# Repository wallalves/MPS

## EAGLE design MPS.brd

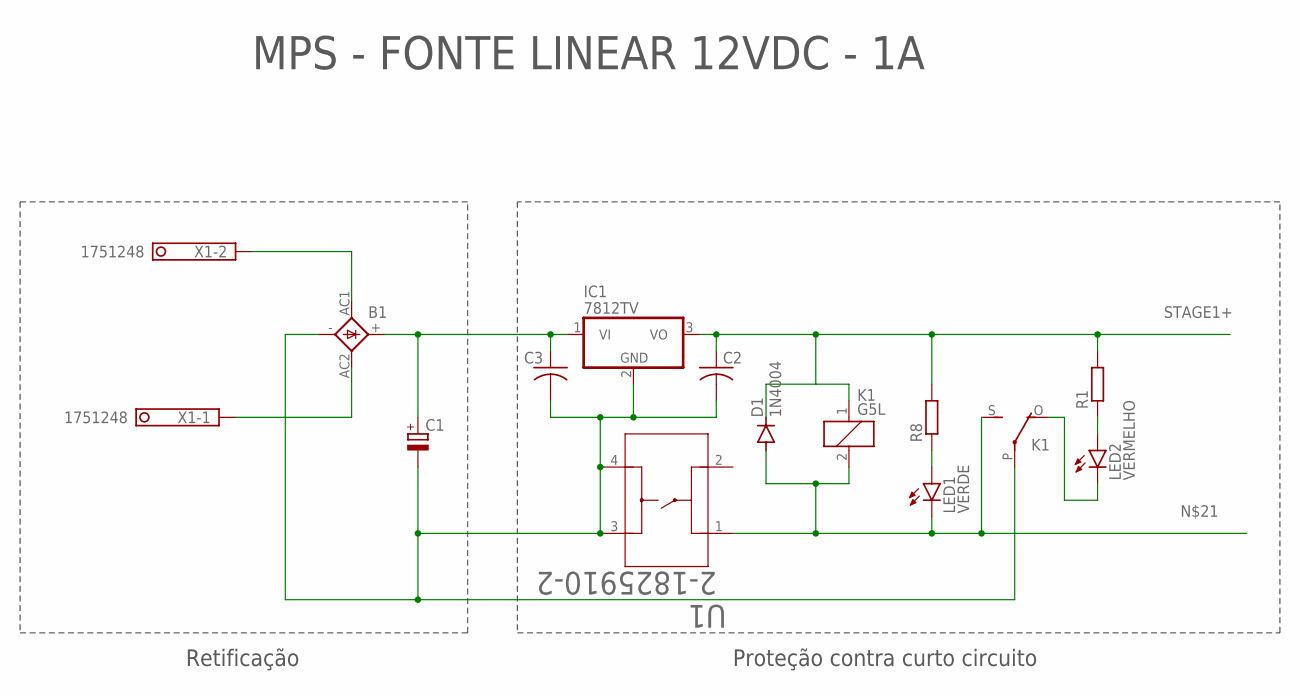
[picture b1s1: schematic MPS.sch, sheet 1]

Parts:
B1: 2KBB-R
C1: CPOL-EUE2.5-7; E2,5-7
C2, C3: C-US050-035X075; C050-035X075
D1: 1N4004; DO41-10
IC1: 7812TV; TO220V
K1: G5L; G5LE
LED1: VERDE; LED3MM
LED2: VERMELHO; LED3MM
R1, R8: R-EU_0207/7; 0207/7
U1: 2-1825910-2; SWITCH_2-1825910-2
X1: 1751248

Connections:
unnamed: B1.AC2, X1.1
unnamed: K1.O, LED2.K (C)
unnamed: LED1.A, R8.1
unnamed: B1.AC1, X1.2
unnamed: LED2.A, R1.1
unnamed: B1.+, C1.+, C3.1, IC1.1 (VI)
unnamed: D1.A, K1.2, K1.S, LED1.K (C), U1.1
STAGE1+: C2.1, D1.C, IC1.3 (VO), K1.1, R1.2, R8.2; also elsewhere on the board
STAGE1-: B1.-, C1.-, C2.2, C3.2, IC1.2 (GND), K1.P, U1.3, U1.4; also elsewhere on the board

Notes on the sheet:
MPS - FONTE LINEAR 12VDC - 1A
Retificação
Proteção contra curto circuito

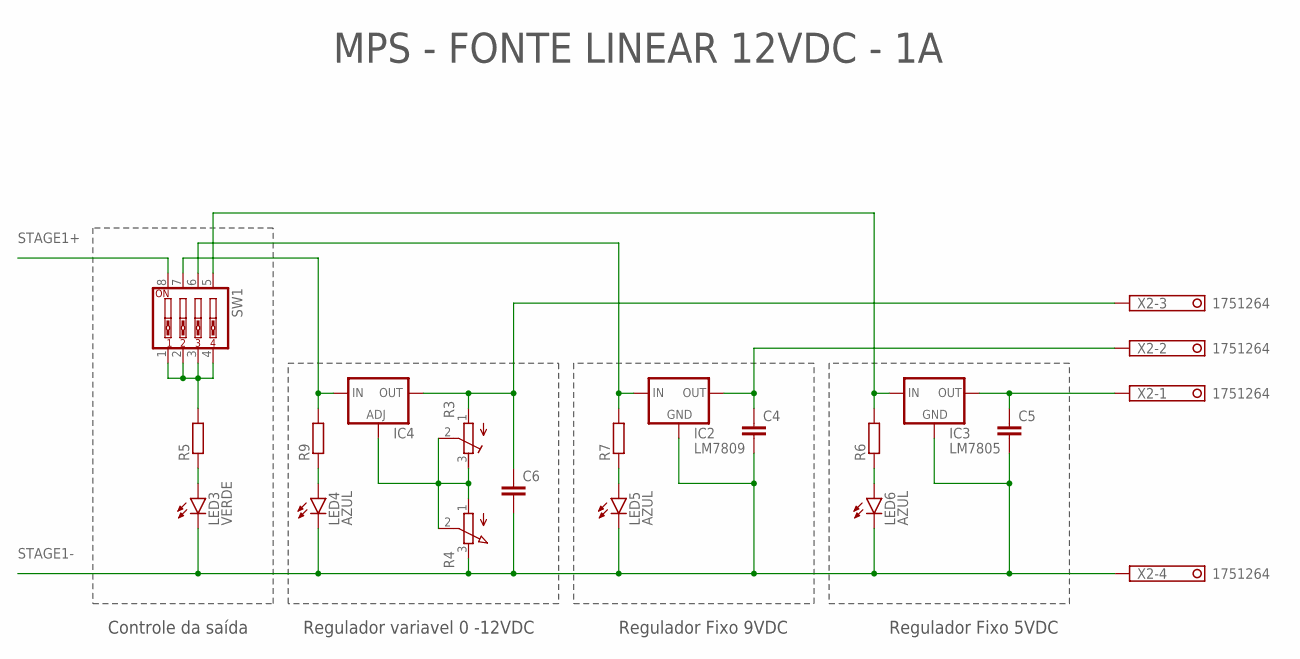
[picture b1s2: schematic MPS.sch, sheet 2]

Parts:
C4, C5, C6: C-EU025-030X050; C025-030X050
IC2: LM7809; 78XXS
IC3: LM7805; 78XXS
IC4: LM317TS; 317TS
LED3: VERDE; LED3MM
LED4, LED5, LED6: AZUL; LED3MM
R3: R-TRIMM64W; RTRIM64W
R4: 3RP/1610N
R5, R6, R7, R9: R-EU_0207/7; 0207/7
SW1: SW_DIP-4; EDG-04
X2: 1751264

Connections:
unnamed: IC4.1 (ADJ), R3.2 (S), R3.3 (E), R4.1 (A), R4.2 (S)
unnamed: C5.1, IC3.OUT, X2.1
unnamed: C4.1, IC2.OUT, X2.2
unnamed: IC4.3 (IN), R9.2, SW1.7
unnamed: LED3.A, R5.1
unnamed: IC2.IN, R7.2, SW1.6
unnamed: IC3.IN, R6.2, SW1.5
unnamed: LED4.A, R9.1
unnamed: LED5.A, R7.1
unnamed: C6.1, IC4.2 (OUT), R3.1 (A), X2.3
unnamed: LED6.A, R6.1
unnamed: R5.2, SW1.1, SW1.2, SW1.3, SW1.4
STAGE1+: SW1.8; also elsewhere on the board
STAGE1-: C4.2, C5.2, C6.2, IC2.GND, IC3.GND, LED3.K (C), LED4.K (C), LED5.K (C), LED6.K (C), R4.3 (E), X2.4; also elsewhere on the board

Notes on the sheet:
MPS - FONTE LINEAR 12VDC - 1A
Regulador Fixo 9VDC
Regulador Fixo 5VDC
Regulador variavel 0 -12VDC
Controle da saída

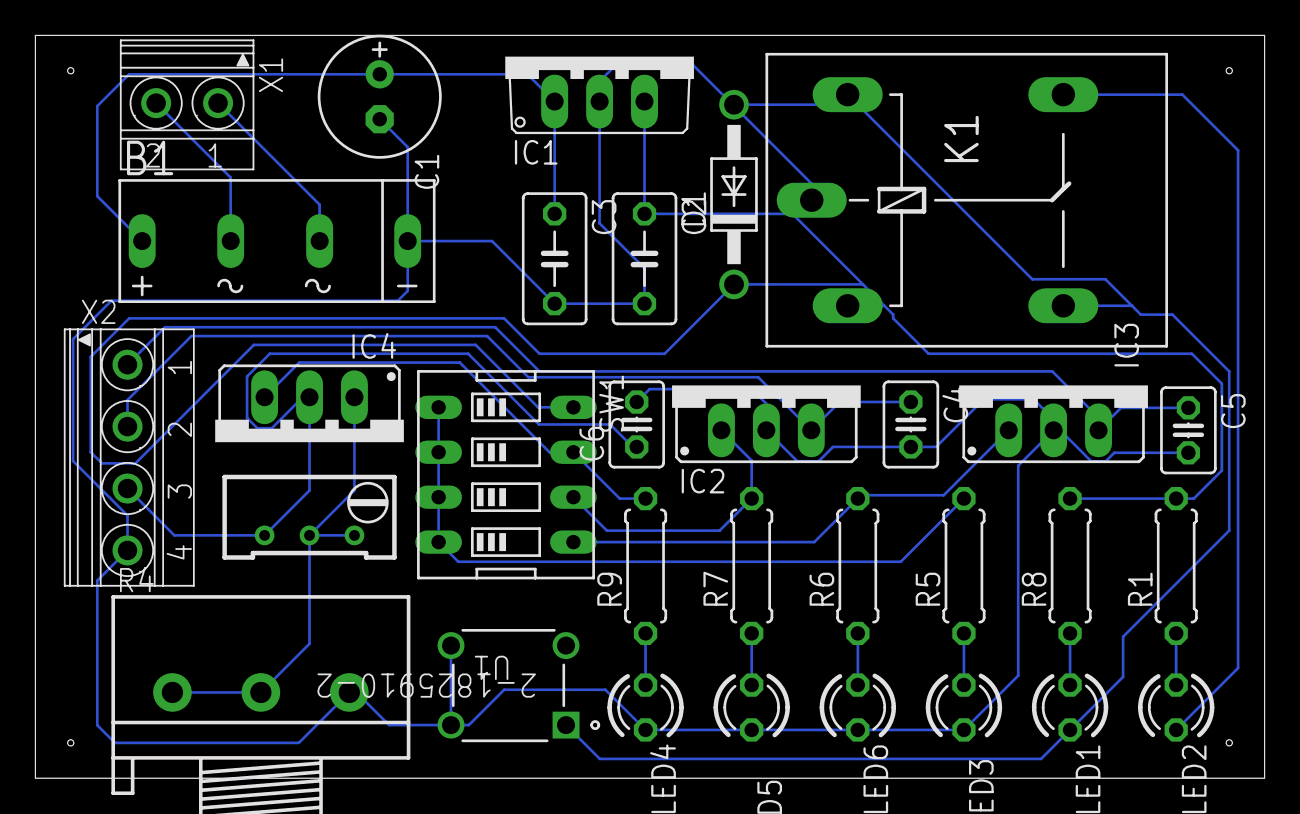
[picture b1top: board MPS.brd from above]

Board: 2 copper layers, 69.5 x 42.0 mm, 31 parts (0 on the bottom side), 21 nets.

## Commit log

2022-10-31 Add files via upload
    FIRST COMIT

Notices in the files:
parts and their libraries:
COPYRIGHT: Copyright (C) 2016 Accelerated Designs. All rights reserved
